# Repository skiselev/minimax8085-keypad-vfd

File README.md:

# minimax8085-keypad-vfd
Keypad and VFD (vacuum fluorescent display) extension board for the MiniMax 8085 SBC

## Introduction

The Keypad and VFD extension board provides simple 20-key keypad and display for [MiniMax8085 SBC](https://github.com/skiselev/minimax8085).
It is designed to be plugged on the top of MiniMax8085 using 2x20 pin header / pin socket.

## Hardware Documentation

### Schematic and PCB Layout

[Schematic - Version 1.0](KiCad/MiniMax8085-Keypad-VFD-Schematic-1.0.pdf)

[PCB Layout - Version 1.0](KiCad/MiniMax8085-Keypad-VFD-Board-1.0.pdf)

### Design Description

#### Address Decode / Chip Select

The Keypad and VFD extension board uses 74HCT138 3-to-8 decoder and 74HCT32 quad 2-input OR gate ICs for address decode:
* Enable signal G1 of 74HCT138 is connected to IO/M signal, and therefore the decoder is enabled only during I/O operations, when IO/M signal value is HIGH
* Enable signals /G2A and /G2B of 74HCT138 are connected to address lines A6 and A7, so that decoder is enabled when both of these signals are low - 0x00 - 0x3F address range
* Inputs A-C of 74HCT138 are connected to address lines A3 - A4, therefore each output of 74HCT138 is active (LOW) for a block of 8 consequitive I/O addresses, /Y0 - for 0x00-0x07, /Y1 - for 0x08-0x0F, ... , /Y6 for 0x30-0x37, and /Y6 for 0x38-0x3F
* Output /Y6 of 74HCT138 is connected to the input of the OR gate U3C, another input of that gate is connected to /RD signal. As the result, the output of the gate U3C - /KPD_RD is active (LOW) during read cycles from 0x30-0x37 I/O range. /KPD_RD is used as the read signal for the keypad encoder
* Output /Y7 of 74HCT138 is connected to inputs of the OR gate U3A and U3B. The second input of the OR gate U3B is connected to /RD signal, so that the output of U3B - /VFD_RD is active (LOW) during read cycles from 0x38-0x3F I/O range. /VFD_RD is used as the read signal for the VFD module. The second input of the OR gate U3A is connected to /WR signal, so that the output of U3A - /VFD_WR is active (LOW) during write cycles to 0x38-0x3F I/O range. /VFD_WR is used as the write signal for the VFD module

#### VFD Interface

The board is designed to interface to a [Noritake CU24025-UW1J](https://www.noritake-elec.com/products/model?part=CU24025-UW1J) or similar VFD module, that is configured in Intel 8000 mode (using a solder link on the module), and the interface is staright-forward:
* Data lines DB0-DB7 of the VFD modules are connected to AD0-AD7 signals
* Register select input RS of the VFD module is connected to address line A0, therefore writing to even addresses in 0x38-0x3F range, writes the command register, while writing or reading odd addresses goes to DDRAM (display memory) or CGRAM (character generator memory)
* /RD and /WR inputs of the VFD module are connected to /VFD_RD and /VFD_WR signals respectfully

#### Keypad Interface

The Keypad and VFD extension board uses [74C923](doc/Fairchild-MM74C922-MM74C923-Datasheet.pdf) 20-key encoder for scanning the keypad. When this IC detects that a keypad button has been pressed, it activates D_AVAIL output, connected to the RST7_5 interrupt signal, resulting in an interrupt to the 8085 CPU. The interrupt service routine can then read the keypad button code from I/O ports in range 0x30-0x37. Only AD0-AD5 data lines are used, therefore the 0x1F AND mask should be applied by the interrupt service routine to the value read from the port.

### Bill of Materials

#### Version 1.0

[MiniMax8085 Keypad and VFD project on Mouser.com](https://www.mouser.com/ProjectManager/ProjectDetail.aspx?AccessID=7fc9d2ae6d) - View and order all components except of the PCB, the VFD module, and the 74C923 20-key encoder.

[MiniMax8085 Keypad and VFD project on OSH Park](https://oshpark.com/shared_projects/jRaDS2Pu) - View and order the PCB.

Component type     | Reference  | Description                                 | Quantity | Possible sources and notes 
------------------ | ---------- | ------------------------------------------- | -------- | --------------------------
PCB                |            | MiniMax 8085 VFD & Keypad PCB               | 1        | Order from a PCB manufacturer of your choice using provided Gerber or KiCad files
Integrated Circut  | U1         | 74C923 20-key encoder, DIP-20               | 1        | eBay
Integrated Circut  | U2         | 74HCT138 3-to-8 line decoder, DIP-16        | 1        | Mouser [595-SN74HCT138N](https://www.mouser.com/ProductDetail/595-SN74HCT138N)<br>Note: Possible replacements: 74LS138, 74HC138, 74ALS138
Integrated Circut  | U3         | 74HCT32 quad 2-input OR gate, DIP-14        | 1        | Mouser [595-SN74HCT32N](https://www.mouser.com/ProductDetail/595-SN74HCT32N)<br>Note: Possible replacements: 74LS32, 74HC32, 74ALS32
IC Socket          | U1         | DIP-20, 300 mil socket                      | 1        | Mouser [517-4820-3000-CP](https://www.mouser.com/ProductDetail/517-4820-3000-CP)
IC Socket          | U2         | DIP-16, 300 mil socket                      | 1        | Mouser [517-4816-3000-CP](https://www.mouser.com/ProductDetail/517-4816-3000-CP)
IC Socket          | U3         | DIP-14, 300 mil socket                      | 1        | Mouser [517-4814-3000-CP](https://www.mouser.com/ProductDetail/517-4814-3000-CP)
Tactile Switch     | SW1 - SW20 | 12x12mm tactile switch, projected type (Omron B3F-4050, Omron B3F-5050) | 20       | Mouser [653-B3F-4050](https://www.mouser.com/ProductDetail/653-B3F-4050), [653-B3F-5050](https://www.mouser.com/ProductDetail/653-B3F-5050)
Switch Key Tops    | SW1 - SW16 | 12x12mm keycap, gray (Omron B32-1300)       | 16       | Mouser [653-B32-1300](https://www.mouser.com/ProductDetail/653-B32-1300)
Switch Key Tops    | SW17       | 12x12mm keycap, blue (Omron B32-1340)       | 1        | Mouser [653-B32-1340](https://www.mouser.com/ProductDetail/653-B32-1340)
Switch Key Tops    | SW18       | 12x12mm keycap, yellow (Omron B32-1330)     | 1        | Mouser [653-B32-1330](https://www.mouser.com/ProductDetail/653-B32-1330)
Switch Key Tops    | SW19       | 12x12mm keycap, red (Omron B32-1380)        | 1        | Mouser [653-B32-1380](https://www.mouser.com/ProductDetail/653-B32-1380)
Switch Key Tops    | SW20       | 12x12mm keycap, green (Omron B32-1350)      | 1        | Mouser [653-B32-1350](https://www.mouser.com/ProductDetail/653-B32-1350)
Header             | P1         | 2x20 pin header, 2.54 mm pitch, straight    | 1        | Mouser [649-67996-140HLF](https://www.mouser.com/ProductDetail/649-67996-140HLF)<br>Note: This header is soldered to the MiniMax 8085 Keypad and VFD board
Header             | P1         | 2x20 socket, 2.54 mm pitch                  | 1        | Mouser [517-929852-01-20-RB](https://www.mouser.com/ProductDetail/517-929852-01-20-RB)<br>Note: This socket is assembled to the MiniMax 8085 board
Header             | P2         | 2x7 pin header, 2.54 mm pitch, right angle  | 1        | Mouser [649-68020-114HLF](https://www.mouser.com/ProductDetail/649-68020-114HLF)
Capacitor          | C1 - C4    | 0.1 µF, MLCC, 5 mm lead spacing             | 4        | Mouser [594-K104K15X7RF53H5](https://www.mouser.com/ProductDetail/594-K104K15X7RF53H5)
Capacitor          | C5         | 1 µF, MLCC, 5 mm lead spacing               | 1        | Mouser [810-FG28X5R1H105KRT0](https://www.mouser.com/ProductDetail/810-FG28X5R1H105KRT0)
Capacitor          | C6         | 10 µF, MLCC, 5 mm lead spacing              | 1        | Mouser [810-FG24X7R1A106KRT0](https://www.mouser.com/ProductDetail/810-FG24X7R1A106KRT0)
VFD Display        |            | 2x24 VFD character display                  | 1        | SurplusGizmos.com [CU24025ECPB-W1J](http://www.surplusgizmos.com/Noritake-Itron-CU24025ECPB-W1J-VFD-Display-Module-2x24-charectors-HD44780_p_2103.html)<br>Note: Can be substituted with other VFD or LCD modules. The module must support Intel i80xx mode.
Header             |            | 2x7 pin header, 2.54 mm pitch, straight     | 1        | Mouser [649-67996-114HLF](https://www.mouser.com/ProductDetail/649-67996-114HLF)<br>Note: Solder this header to the VFD module
Connector          |            | 2x7 pin IDC socket, 2.54 mm pitch           | 2        | Mouser [517-D89114-0131HK](https://www.mouser.com/ProductDetail/517-D89114-0131HK)
Cable              |            | 14 wire ribbon cable, 28AWG                 | 1 ft.    | Mouser [517-3365-14FT](https://www.mouser.com/ProductDetail/517-3365-14FT)

## Programming Keypad and VFD Extension Board

### Keypad

The [74C923](doc/Fairchild-MM74C922-MM74C923-Datasheet.pdf) keypad encoder is connected to the 8085 processor so that it generates RST 7.5 interrupt when a key is pressed. The key code then can be read from the I/O port 0x30. Only lower 5 bits are used for the key code, and the upper 3 bits are undefined, therefore it is recommended to AND the read value with 0x1F mask. For example:
<pre><code>
        IN      30h
        ANI     1Fh
</code></pre>
Before using keypad, make sure to unmask RST 7.5 and enable interrupts:
<pre><code>
        MVI     A,1Bh    ; 1Bh = 00011011b - Reset RST 7.5 flip-flop, set interrupt mask, unmask RST 7.5, keep RST 5.5 and RST 6.5 masked
        SIM              ; set interrupt mask
        EI               ; enable interrupts
</code></pre>

### VFD

The [Noritake CU24025-UW1J](https://www.noritake-elec.com/products/model?part=CU24025-UW1J) and similar VFD displays are programmed similarly to LCD displays based on [Hitachi HD44780 LCD controller](https://en.wikipedia.org/wiki/Hitachi_HD44780_LCD_controller). The programming infromation is available in [Noritake CU24025-UW1J datasheet](doc/Noritake-CU24025-UW1J-Datasheet.pdf). Multiple Hitachi HD44780 programming examples are also available in the Internet.

The VFD display uses two I/O ports:
* 0x38 - VFD_CMD - used to write commands to the VFD controller, and read back the *BUSY* flag and the *address counter*
* 0x39 - VFD_DATA - used to write data to the VFD controller's display memory (DDRAM) or character generator memory (CGRAM)

#### VFD Initialization
Prior to displaying text, the VFD display needs to be initialized by sending the following commands (see the [Noritake CU24025-UW1J datasheet](doc/Noritake-CU24025-UW1J-Datasheet.pdf) for more details and options):
1. Write 0x38 to VFD_CMD: Function Set: 8-bit interface; Two lines; 5x7 characters
2. Write 0x0C to VFD_CMD: Display on/off control: Display power on; No cursor; No cursor blink
3. Write 0x01 to VFD_CMD: Clear display; Return cursor to the home position
4. Write 0x06 to VFD_CMD: Entry Mode: Left to Right; No scroll

After this initialization sequence, the characters written to port VFD_DATA will be displayed on the VFD.

#### Using programmable character generator
The VFD provides eight user-programmable characters. These characters have ASCII codes from 0 to 7. The VFD controller contains Character Generator RAM (CGRAM) that holds the bitmaps for the user-programmable characters. The CGRAM can be programmed by sending "Set CGRAM address" command. This command's code is 0x40 + CGRAM address. Here are the "Set CGRAM address" commands with corresponding addresses for each of the user programmable characters:
* 0x40 to 0x47 - character with code 0
* 0x48 to 0x4F - character with code 1
* 0x50 to 0x57 - character with code 2
* 0x58 to 0x5F - character with code 3
* 0x60 to 0x67 - character with code 4
* 0x68 to 0x6F - character with code 5
* 0x70 to 0x77 - character with code 6
* 0x78 to 0x7F - character with code 7

After issuing "Set CGRAM address" command, the character bit map can be set using port 0x39. After writing each byte the CGRAM address is automatically incremented by the controller. Here is an example of programming a smiley face character:
Character bitmap:

Pixels | Binary	| Hexadecimal
------ | ------ | ----------- 
 ░░░░░ | 00000 | 0x00
 ░█░█░| 01010 | 0x0A
 ░░░░░| 00000 | 0x00
 ░░░░░| 00000 | 0x00
 █░░░█| 10001 | 0x11
 ░███░| 01110 | 0x0E
 ░░░░░| 00000 | 0x00

Commands to program the character in MON85:
* C> **o 38 80** - set DDRAM to the first character
* C> **o 39 00** - print the first programmable character
* C> **o 38 40** - set CGRAM to the first programmable character
* C> **o 39 00** - character data - upper row
* C> **o 39 0A** - character data - 2nd row
* C> **o 39 00** - character data - 3rd row
* C> **o 39 00** - character data - 4th row
* C> **o 39 11** - character data - 5th row
* C> **o 39 0E** - character data - 6th row
* C> **o 39 00** - character data - 7th row
* C> **o 39 00** - no underline
* C> **o 38 81** - set DDRAM to the correct position because modifying CGRAM moves the cursor

### Keypad and VFD Sample Code

The [keypad_vfd.asm](software/keypad_vfd.asm) sample reads pressed key from the keypad and prints it on the VFD display. It consists of the following parts:
* Initialization:
  * Sets the inital stack pointer (SP) value. This is needed when the sample is run directly from ROM
  * Calls USART_INIT subroutine to initialize the Intel 8251 USART
  * Calls VFD_INIT subroutine to initialize the VFD
  * Unmasks RST 7.5 interrupt and enables interrupts
* Loop:
  * Calls USART_IN to read a character from USART
  * Compares that to ESC code, and exists to MON85 by calling RST 0 if that is the case
* Keypad / RST 7.5 interrupt handler:
  * Reads key code from keypad
  * Calculates the corresponding ASCII character code
  * Outputs the character to USART using USART_OUT subroutine
  * Outputs the character to VFD using VFD_SEND_DATA subroutine
  * Re-enables interrupts and returns
* Generic routines for USART and VFD initialization and I/O
  * USART_INIT subroutine - initializes the Intel 8251 USART
  * USART_IN subroutine - waits for a character to be recieved by the UART, reads and returns it
  * USART_OUT subroutine - sends the character using the UART
  * VFD_INIT subroutine - initializes the VFD, clears the display, and sets cursor parameters
  * VFD_SEND_CMD subroutine - writes command to the VFD
  * VFD_SEND_DATA subroutine - writes data byte to the VFD

#### Running the sample from MON85

Use the following commands to run the sample:
* C> **L** - Load hex file. Type *L* following by *Enter*, then copy and paste the content of [keypad_vfd.hex](software/keypad_vfd.hex) file. This will load the sample to the RAM starting at 0x8000
* C> **U 8000** - Set user area. This command sets RST vectors redirection to 0x8000. This way when the keypad generates RST 7.5 hardware interrupt, it will call 803Ch location
* C> **G 8000** - Runs the code starting at 0x8000
* Push buttons on the keypad, they should be printed on the VFD screen as well as on the serial console. Press *ESC* button on the keyboard to exit the sample and return to MON85

#### Files
* [keypad_vfd.asm](software/keypad_vfd.asm)
* [keypad_vfd.hex](software/keypad_vfd.hex)

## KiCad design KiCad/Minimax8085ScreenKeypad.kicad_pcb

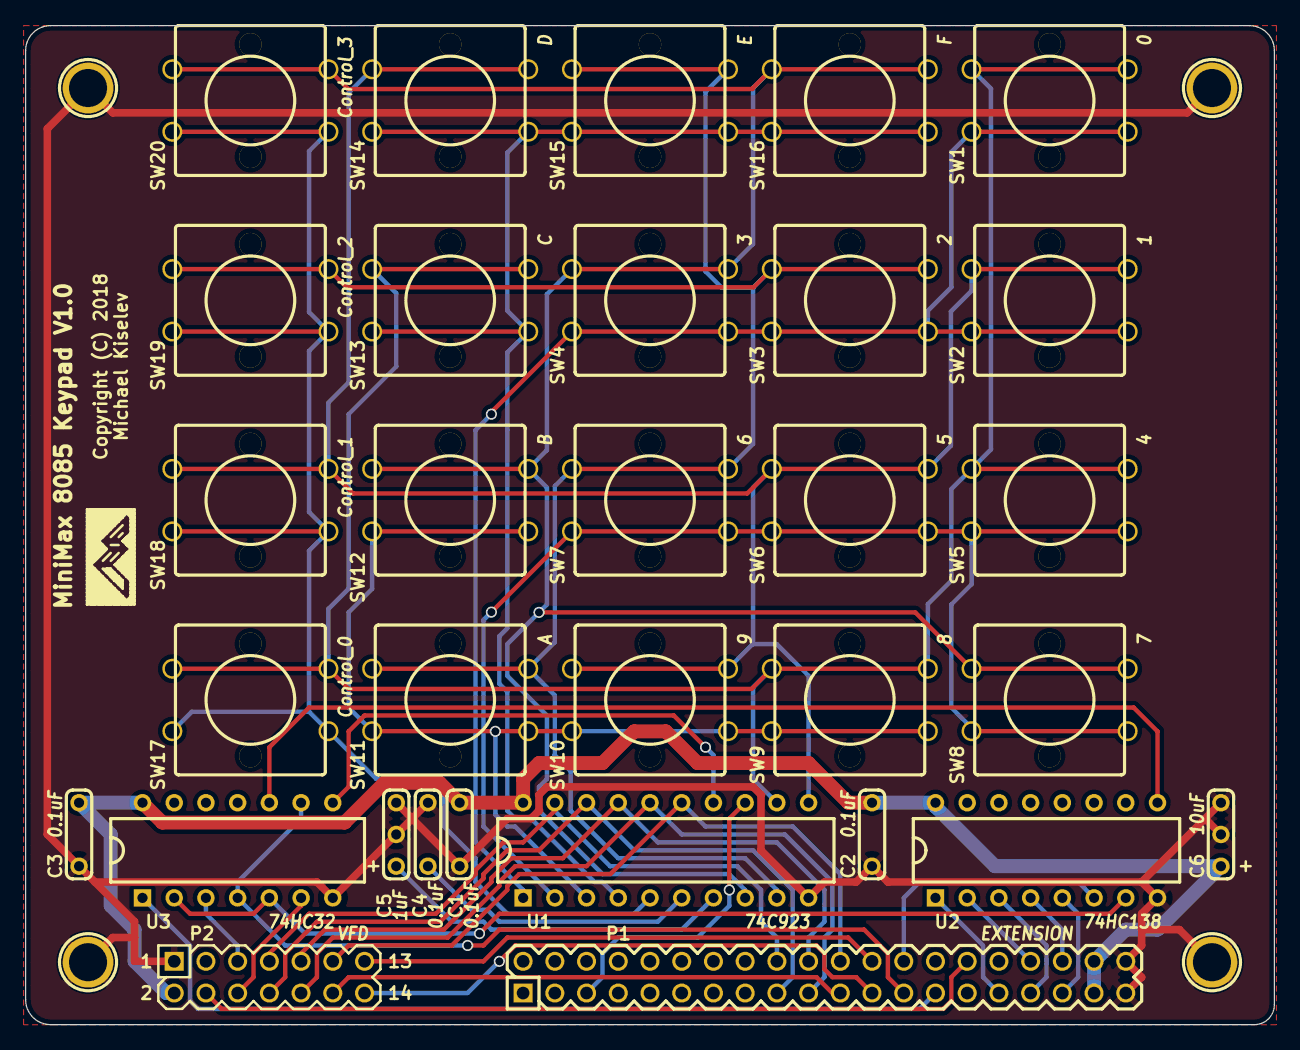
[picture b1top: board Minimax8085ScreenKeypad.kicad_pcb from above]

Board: 2 copper layers, 100.0 x 80.0 mm, 35 parts (1 on the bottom side), 36 nets.

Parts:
C1, C2, C3, C4: 0.1uF; Cap_Cer_508
C5: 1uF; Cap_Pol_508_3
C6: 10uF; Cap_Pol_508_3
HOLE1, HOLE2, HOLE3, HOLE4: HOLE; Hole_3mm
P1: EXTENSION; Conn_Pin_Header_20x2_2.54mm
P2: VFD; Conn_Pin_Header_7x2_2.54mm
SW1: 0; Switch_Tactile_12mm
SW2: 1; Switch_Tactile_12mm
SW3: 2; Switch_Tactile_12mm
SW4: 3; Switch_Tactile_12mm
SW5: 4; Switch_Tactile_12mm
SW6: 5; Switch_Tactile_12mm
SW7: 6; Switch_Tactile_12mm
SW8: 7; Switch_Tactile_12mm
SW9: 8; Switch_Tactile_12mm
SW10: 9; Switch_Tactile_12mm
SW11: A; Switch_Tactile_12mm
SW12: B; Switch_Tactile_12mm
SW13: C; Switch_Tactile_12mm
SW14: D; Switch_Tactile_12mm
SW15: E; Switch_Tactile_12mm
SW16: F; Switch_Tactile_12mm
SW17: Control_0; Switch_Tactile_12mm
SW18: Control_1; Switch_Tactile_12mm
SW19: Control_2; Switch_Tactile_12mm
SW20: Control_3; Switch_Tactile_12mm
U1: 74C923; IC_DIP20_300
U2: 74HC138; IC_DIP16_300
U3: 74HC32; IC_DIP14_300

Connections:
/A0: P1.30, P2.4
/A3: P1.31, U2.1
/A4: P1.34, U2.2
/A5: P1.33, U2.3
/A6: P1.36, U2.4
/A7: P1.35, U2.5
/AD0: P1.18, P2.7, U1.19
/AD1: P1.17, P2.8, U1.18
/AD2: P1.20, P2.9, U1.17
/AD3: P1.19, P2.10, U1.16
/AD4: P1.22, P2.11, U1.15
/AD5: P1.21, P2.12
/AD6: P1.24, P2.13
/AD7: P1.23, P2.14
/IO/~M: P1.26, U2.6
/RST7_5: P1.5, U1.13
/~KPD_CS: U2.9, U3.10
/~KPD_RD: U1.14, U3.8
/~RD: P1.25, U3.4, U3.9
/~VFD_CS: U2.7, U3.2, U3.5
/~VFD_RD: P2.6, U3.6
/~VFD_WR: P2.5, U3.3
/~WR: P1.27, U3.1
GND: C1.2, C2.2, C3.2, C4.2, C5.2, C6.2, HOLE1.1, HOLE2.1, HOLE3.1, HOLE4.1, P1.39, P1.40, P2.1, U1.10, U2.8, U3.7
unnamed: C4.1, U1.6
unnamed: C5.1, U1.7
unnamed: SW1.1, SW5.1, SW9.1, SW13.1, SW17.1, U1.12
unnamed: SW1.2, SW2.2, SW3.2, SW4.2, U1.1
unnamed: SW5.2, SW6.2, SW7.2, SW8.2, U1.2
unnamed: SW2.1, SW6.1, SW10.1, SW14.1, SW18.1, U1.11
unnamed: SW9.2, SW10.2, SW11.2, SW12.2, U1.3
unnamed: SW3.1, SW7.1, SW11.1, SW15.1, SW19.1, U1.9
unnamed: SW4.1, SW8.1, SW12.1, SW16.1, SW20.1, U1.8
unnamed: SW13.2, SW14.2, SW15.2, SW16.2, U1.4
unnamed: SW17.2, SW18.2, SW19.2, SW20.2, U1.5
VCC: C1.1, C2.1, C3.1, C6.1, P1.37, P1.38, P2.2, U1.20, U2.16, U3.14

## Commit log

2019-03-22 Added CAD Files
2019-03-23 added BOM
2019-03-23 Added PDFs
2019-03-23 added PDF links
2019-04-01 README: Update BOM
2019-04-01 README: Fix markdown formatting
2019-04-01 README: Add the photo of the board
2019-04-03 README: U1 is DIP-20
2021-09-24 Add design description
2021-09-28 README: Add Keypad and VFD Sample Code
2021-09-28 Add programming sample
2021-09-28 software: Fix MON85 command
2021-09-28 README: Add programming information
2021-09-28 software: fix VFD initialization
2021-09-28 Add datasheets

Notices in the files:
KiCad/Minimax8085ScreenKeypad.kicad_pcb:
Copyright (C) 2018
